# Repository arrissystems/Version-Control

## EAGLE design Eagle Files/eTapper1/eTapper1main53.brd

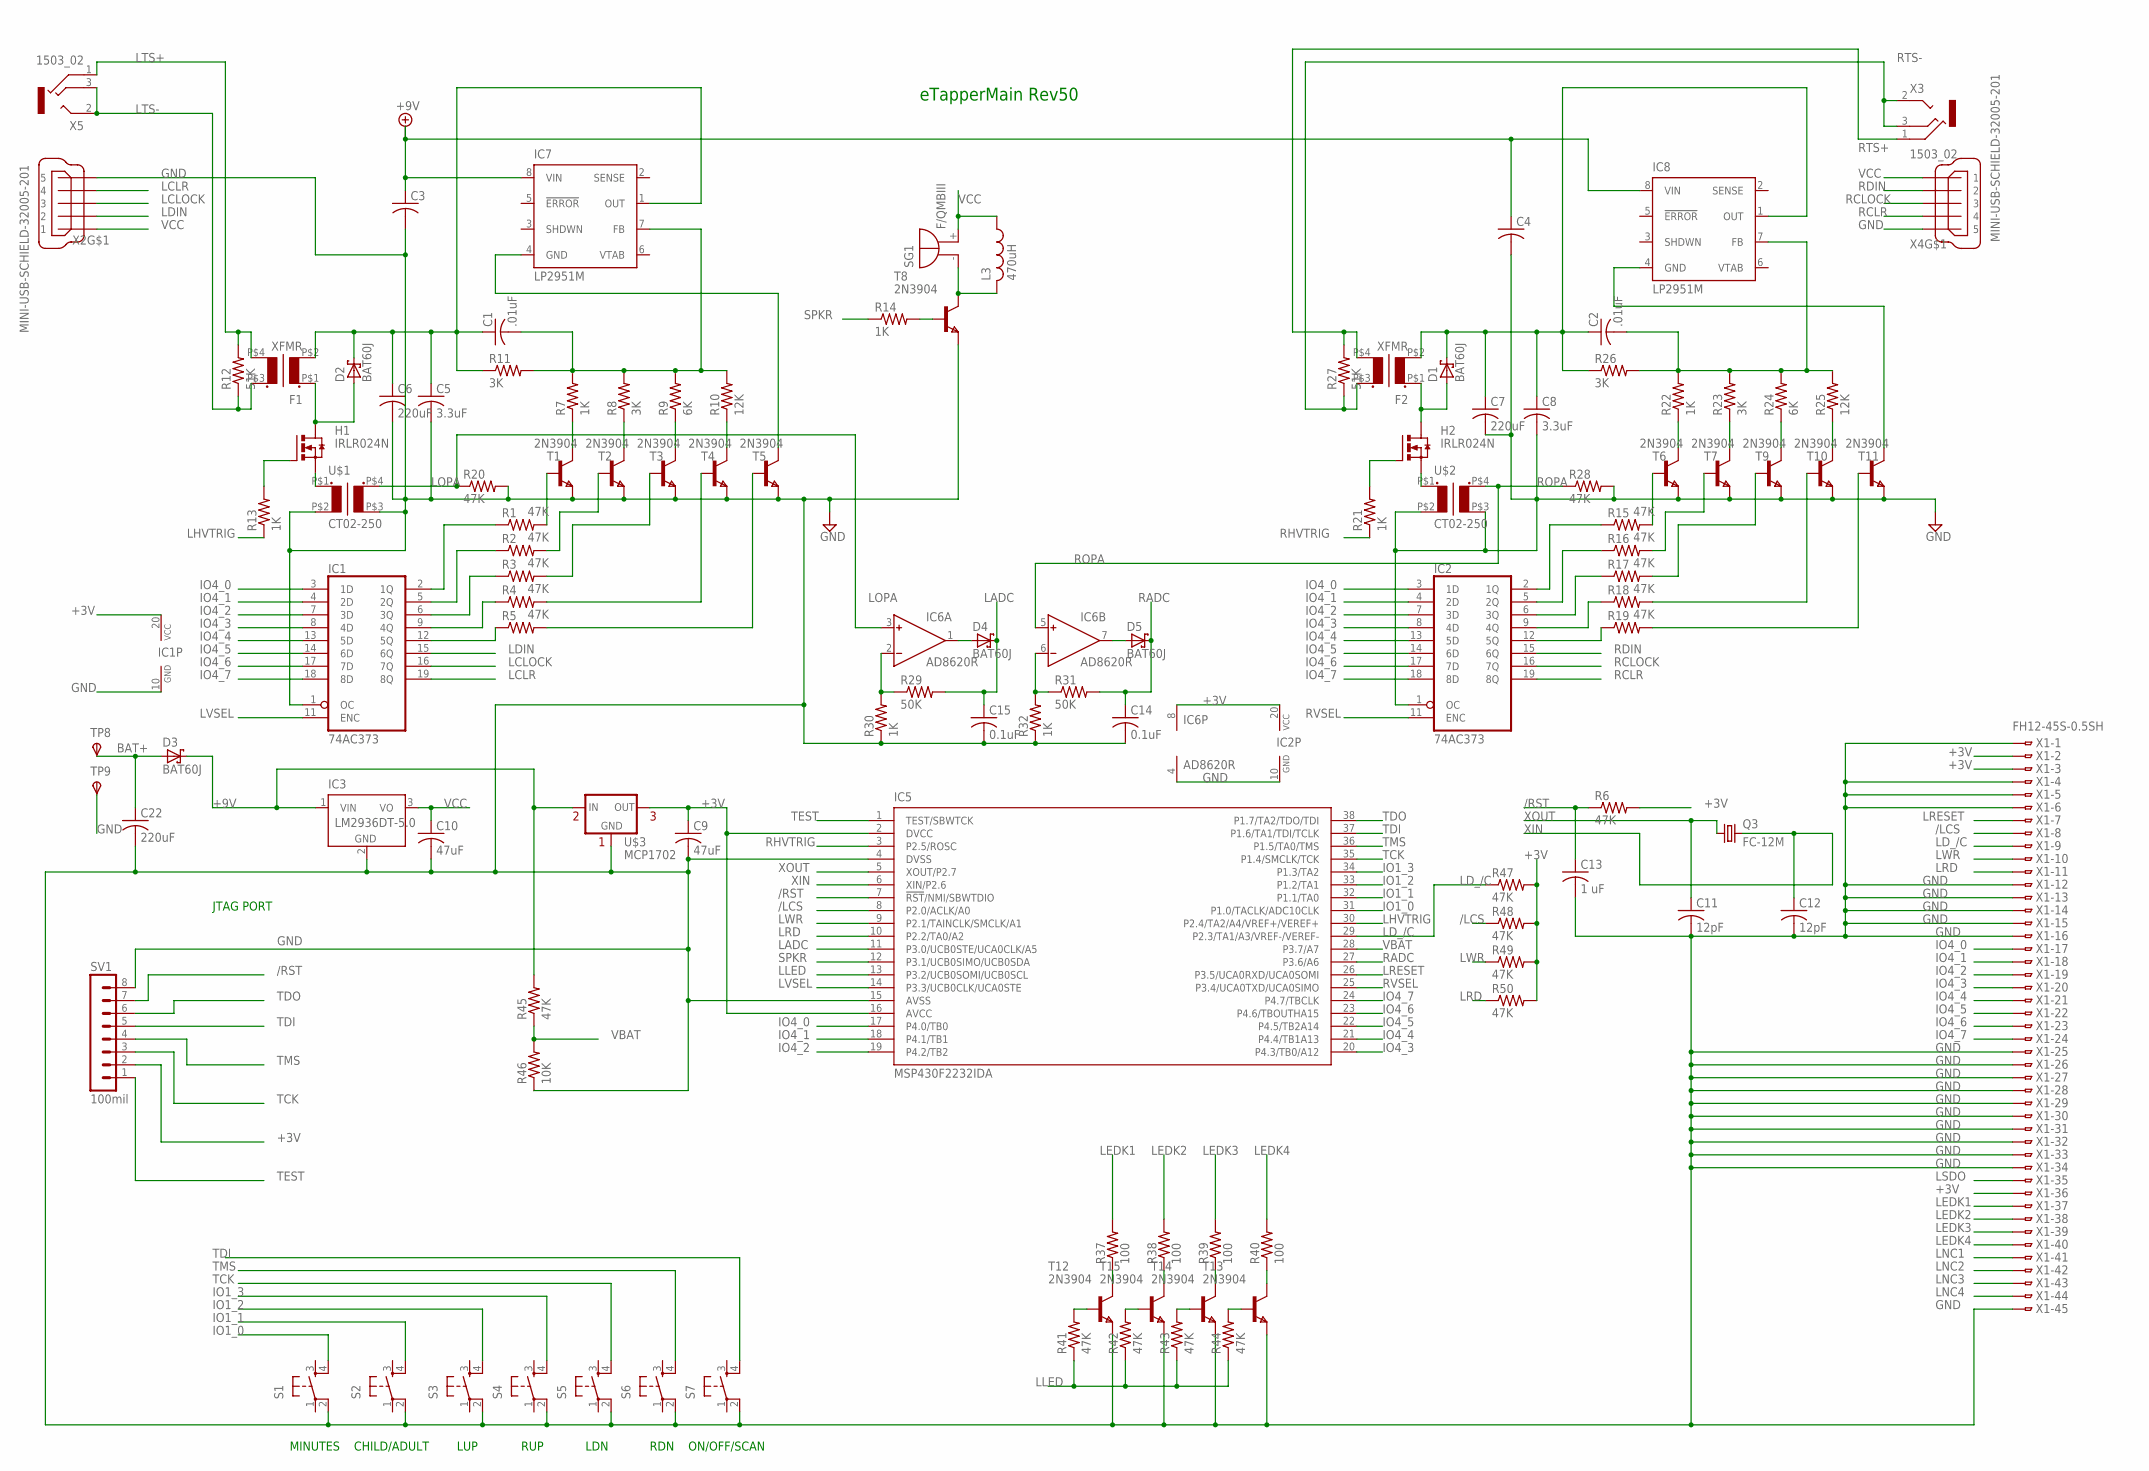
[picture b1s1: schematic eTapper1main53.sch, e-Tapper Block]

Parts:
C1, C2: .01uF; C0805
C3, C4: C-USC1206; C1206
C5, C8: 3.3uF; C0805
C6, C7, C22: 220uF; C1206
C9, C10: 47uF; C1206
C11, C12: 12pF; C0805
C13: 1 uF; C0805
C14, C15: 0.1uF; C0805
D1, D2, D3, D4, D5: BAT60J; SOD323_ST
F1, F2: XFMR
H1, H2: IRLR024N; D-PAK_TO252AA
IC1, IC2: 74AC373; SO20
IC3: LM2936DT-5.0; TO252
IC5: MSP430F2232IDA; TSSOP38_R-PDSO-G38-DA
IC6: AD8620R; SO8
IC7, IC8: LP2951M; SO08
L3: 470uH; L2825P
Q3: FC-12M
R1, R2, R3, R4, R5, R6, R15, R16, R17, R18, R19, R20, R28, R41, R42, R43, R44, R45, R47, R48, R49, R50: 47K; R0603
R7, R13, R14, R21, R22, R30, R32: 1K; R0603
R8, R11, R23, R26: 3K; R0603
R9, R24: 6K; R0603
R10, R25: 12K; R0603
R12, R27: 51K; R0603
R29, R31: 50K; R0603
R37, R38, R39, R40: 100; R0603
R46: 10K; R0603
S1, S2, S3, S4, S5, S6, S7: 10-XX; B3F-10XX
SG1: F/QMBIII
SV1: 100mil; MA08-1
T1, T2, T3, T4, T5, T6, T7, T8, T9, T10, T11, T12, T13, T14, T15: 2N3904; SOT-23
TP8, TP9: TPSPAD1-20; P1-20
U$1, U$2: CT02-250
U$3: MCP1702; TO92-
X1: FH12-45S-0.5SH
X2, X4: MINI-USB-SCHIELD-32005-201; 32005-201
X3, X5: 1503_02

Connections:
+3V: C9.1, IC1.20 (VCC), IC2.20 (VCC), IC5.2 (DVCC), IC5.16 (AVCC), IC6.8 (V+), R6.2, R47.2, R48.2, R49.2, R50.2, SV1.2, U$3.3 (OUT), X1.2, X1.3, X1.36
+9V: C3.1, C4.1, D3.C, IC3.1 (VIN), IC7.8 (VIN), IC8.8 (VIN), R45.2, U$3.2 (IN)
/LCS: IC5.8 (P2.0/ACLK/A0), R48.1, X1.8
/RST: C13.1, IC5.7 (!RST!/NMI/SBWTDIO), R6.1, SV1.7
BAT+: C22.1, D3.A, TP8.TP
GND: C3.2, C4.2, C5.2, C6.2, C7.2, C8.2, C9.2, C10.2, C11.2, C12.2, C13.2, C14.2, C15.2, C22.2, IC1.1 (OC), IC1.10 (GND), IC2.1 (OC), IC2.10 (GND), IC3.2 (GND), IC5.4 (DVSS), IC5.15 (AVSS), IC6.4 (V-), R20.2, R28.2, R30.1, R32.1, R46.1, S1.2 (P1), S2.2 (P1), S3.2 (P1), S4.2 (P1), S5.2 (P1), S6.2 (P1), S7.2 (P1), SV1.8, T1.2 (E), T2.2 (E), T3.2 (E), T4.2 (E), T5.2 (E), T6.2 (E), T7.2 (E), T8.2 (E), T9.2 (E), T10.2 (E), T11.2 (E), T12.2 (E), T13.2 (E), T14.2 (E), T15.2 (E), TP9.TP, U$1.P$2 (P2), U$1.P$3 (S2), U$2.P$2 (P2), U$2.P$3 (S2), U$3.1 (GND), X1.1, X1.4, X1.5, X1.6, X1.12, X1.13, X1.14, X1.15, X1.16, X1.25, X1.26, X1.27, X1.28, X1.29, X1.30, X1.31, X1.32, X1.33, X1.34, X1.45, X2.5, X4.5
IO1_0: IC5.31 (P1.0/TACLK/ADC10CLK), S1.4 (S1)
IO1_1: IC5.32 (P1.1/TA0), S2.4 (S1)
IO1_2: IC5.33 (P1.2/TA1), S3.4 (S1)
IO1_3: IC5.34 (P1.3/TA2), S4.4 (S1)
IO4_0: IC1.3 (1D), IC2.3 (1D), IC5.17 (P4.0/TB0), X1.17
IO4_1: IC1.4 (2D), IC2.4 (2D), IC5.18 (P4.1/TB1), X1.18
IO4_2: IC1.7 (3D), IC2.7 (3D), IC5.19 (P4.2/TB2), X1.19
IO4_3: IC1.8 (4D), IC2.8 (4D), IC5.20 (P4.3/TB0/A12), X1.20
IO4_4: IC1.13 (5D), IC2.13 (5D), IC5.21 (P4.4/TB1A13), X1.21
IO4_5: IC1.14 (6D), IC2.14 (6D), IC5.22 (P4.5/TB2A14), X1.22
IO4_6: IC1.17 (7D), IC2.17 (7D), IC5.23 (P4.6/TBOUTHA15), X1.23
IO4_7: IC1.18 (8D), IC2.18 (8D), IC5.24 (P4.7/TBCLK), X1.24
LADC: C15.1, D4.C, IC5.11 (P3.0/UCB0STE/UCA0CLK/A5), R29.2
LCLOCK: IC1.16 (7Q), X2.3
LCLR: IC1.19 (8Q), X2.4
LDIN: IC1.15 (6Q), X2.2
LD_/C: IC5.29 (P2.3/TA1/A3/VREF-/VEREF-), R47.1, X1.9
LEDK1: R37.2, X1.37
LEDK2: R38.2, X1.38
LEDK3: R39.2, X1.39
LEDK4: R40.2, X1.40
LHVTRIG: IC5.30 (P2.4/TA2/A4/VREF+/VEREF+), R13.1
LLED: IC5.13 (P3.2/UCB0SOMI/UCB0SCL), R41.1, R42.1, R43.1, R44.1
LNC1: X1.41
LNC2: X1.42
LNC3: X1.43
LNC4: X1.44
LOPA: IC6.3 (IN+), R20.1, U$1.P$4 (S1)
LRD: IC5.10 (P2.2/TA0/A2), R50.1, X1.11
LRESET: IC5.26 (P3.5/UCA0RXD/UCA0SOMI), X1.7
LSDO: X1.35
LTS+: F1.P$4 (S2), R12.2, X5.1
LTS-: F1.P$3 (S1), R12.1, X5.2, X5.3
LVSEL: IC1.11 (ENC), IC5.14 (P3.3/UCB0CLK/UCA0STE)
LWR: IC5.9 (P2.1/TAINCLK/SMCLK/A1), R49.1, X1.10
unnamed: IC1.2 (1Q), R1.1
unnamed: IC1.5 (2Q), R2.1
unnamed: IC1.6 (3Q), R3.1
unnamed: IC1.9 (4Q), R4.1
unnamed: IC1.12 (5Q), R5.1
unnamed: L3.2, SG1.- (+), T8.1 (C)
unnamed: R4.2, T4.3 (B)
unnamed: R5.2, T5.3 (B)
unnamed: D2.A, F1.P$1 (P1), H1.4 (D)
unnamed: R7.1, T1.1 (C)
unnamed: R8.1, T2.1 (C)
unnamed: R9.1, T3.1 (C)
unnamed: R1.2, T1.3 (B)
unnamed: R2.2, T2.3 (B)
unnamed: R3.2, T3.3 (B)
unnamed: R10.1, T4.1 (C)
unnamed: C1.2, IC7.7 (FB), R7.2, R8.2, R9.2, R10.2, R11.2
unnamed: C1.1, C5.1, C6.1, D2.C, F1.P$2 (P2), IC7.1 (OUT), R11.1
unnamed: D1.A, F2.P$1 (P1), H2.4 (D)
unnamed: IC2.2 (1Q), R15.1
unnamed: H1.1 (G), R13.2
unnamed: R14.2, T8.3 (B)
unnamed: H1.3 (S), U$1.P$1 (P1)
unnamed: IC2.5 (2Q), R16.1
unnamed: IC2.6 (3Q), R17.1
unnamed: IC2.9 (4Q), R18.1
unnamed: IC2.12 (5Q), R19.1
unnamed: R44.2, T13.3 (B)
unnamed: R15.2, T6.3 (B)
unnamed: R16.2, T7.3 (B)
unnamed: R17.2, T9.3 (B)
unnamed: R18.2, T10.3 (B)
unnamed: R19.2, T11.3 (B)
unnamed: D4.A, IC6.1 (OUT)
unnamed: R22.1, T6.1 (C)
unnamed: R23.1, T7.1 (C)
unnamed: R24.1, T9.1 (C)
unnamed: R25.1, T10.1 (C)
unnamed: C2.2, IC8.7 (FB), R22.2, R23.2, R24.2, R25.2, R26.2
unnamed: C2.1, C7.1, C8.1, D1.C, F2.P$2 (P2), IC8.1 (OUT), R26.1
unnamed: R37.1, T12.1 (C)
unnamed: H2.1 (G), R21.2
unnamed: R38.1, T15.1 (C)
unnamed: R39.1, T14.1 (C)
unnamed: IC7.4 (GND), T5.1 (C)
unnamed: R40.1, T13.1 (C)
unnamed: IC8.4 (GND), T11.1 (C)
unnamed: R43.2, T14.3 (B)
unnamed: R41.2, T12.3 (B)
unnamed: R42.2, T15.3 (B)
unnamed: H2.3 (S), U$2.P$1 (P1)
unnamed: IC6.6 (IN-), R31.1, R32.2
unnamed: IC6.2 (IN-), R29.1, R30.2
unnamed: D5.A, IC6.7 (OUT)
RADC: C14.1, D5.C, IC5.27 (P3.6/A6), R31.2
RCLOCK: IC2.16 (7Q), X4.3
RCLR: IC2.19 (8Q), X4.4
RDIN: IC2.15 (6Q), X4.2
RHVTRIG: IC5.3 (P2.5/ROSC), R21.1
ROPA: IC6.5 (IN+), R28.1, U$2.P$4 (S1)
RTS+: F2.P$4 (S2), R27.2, X3.1
RTS-: F2.P$3 (S1), R27.1, X3.2, X3.3
RVSEL: IC2.11 (ENC), IC5.25 (P3.4/UCA0TXD/UCA0SIMO)
SPKR: IC5.12 (P3.1/UCB0SIMO/UCB0SDA), R14.1
TCK: IC5.35 (P1.4/SMCLK/TCK), S5.4 (S1), SV1.3
TDI: IC5.37 (P1.6/TA1/TDI/TCLK), S7.4 (S1), SV1.5
TDO: IC5.38 (P1.7/TA2/TDO/TDI), SV1.6
TEST: IC5.1 (TEST/SBWTCK), SV1.1
TMS: IC5.36 (P1.5/TA0/TMS), S6.4 (S1), SV1.4
VBAT: IC5.28 (P3.7/A7), R45.1, R46.2
VCC: C10.1, IC3.3 (VO), L3.1, SG1.+ (-), X2.1, X4.1
XIN: C12.1, IC5.6 (XIN/P2.6), Q3.2
XOUT: C11.1, IC5.5 (XOUT/P2.7), Q3.1

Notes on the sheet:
ON/OFF/SCAN
MINUTES
CHILD/ADULT
LUP
RUP
JTAG PORT
LDN
RDN
eTapperMain Rev50

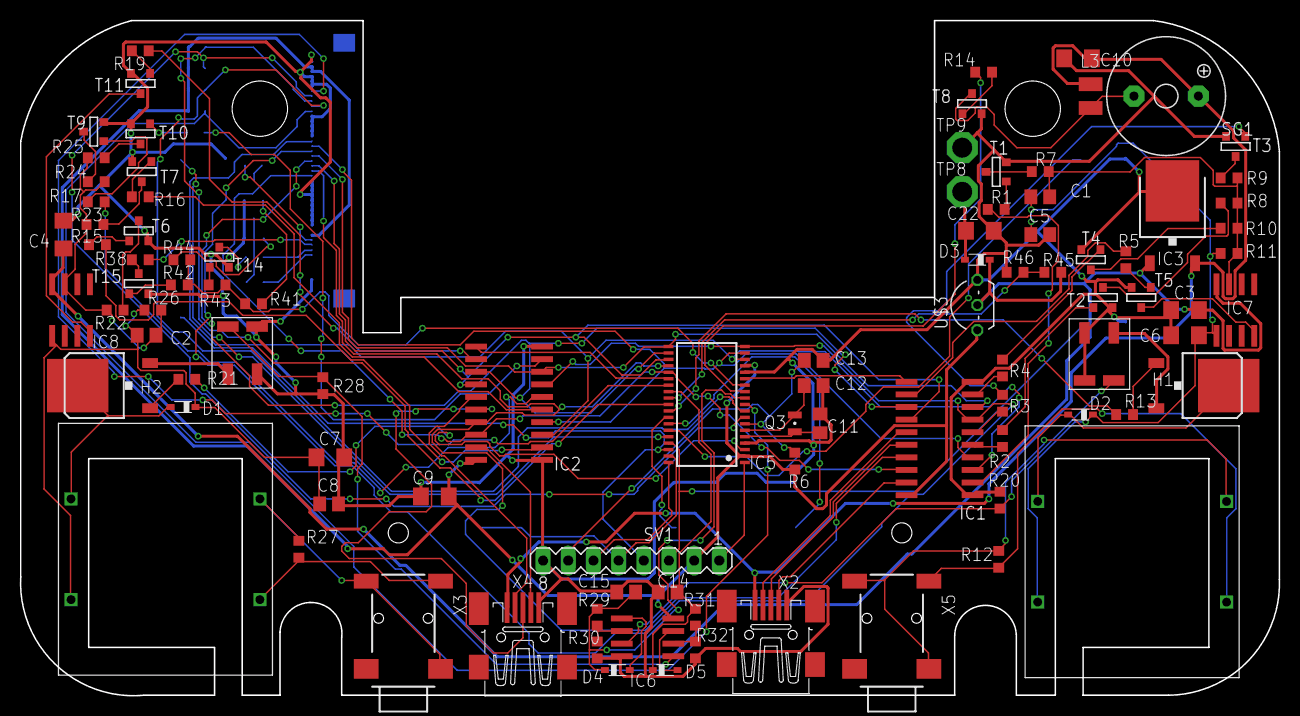
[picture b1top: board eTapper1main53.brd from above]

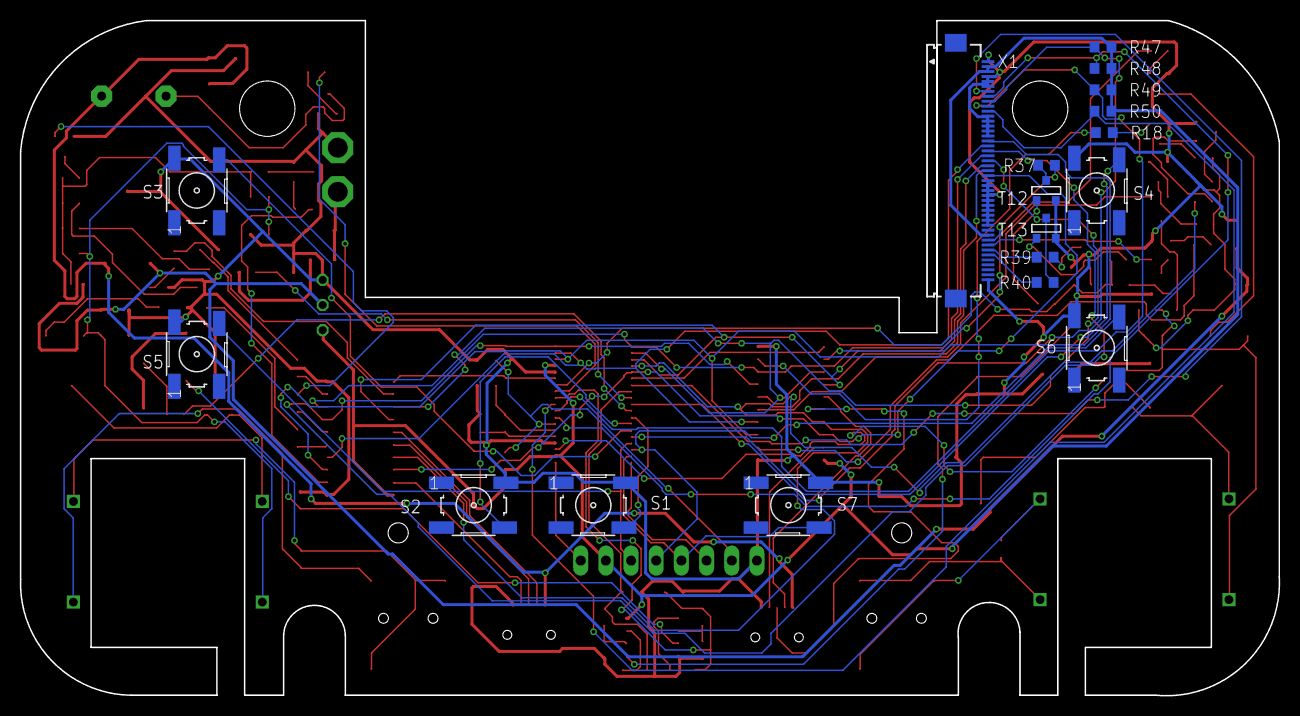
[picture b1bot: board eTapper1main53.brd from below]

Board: 2 copper layers, 127.0 x 68.1 mm, 115 parts (18 on the bottom side), 109 nets.

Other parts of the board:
DRILEGEND: DRILEGEND

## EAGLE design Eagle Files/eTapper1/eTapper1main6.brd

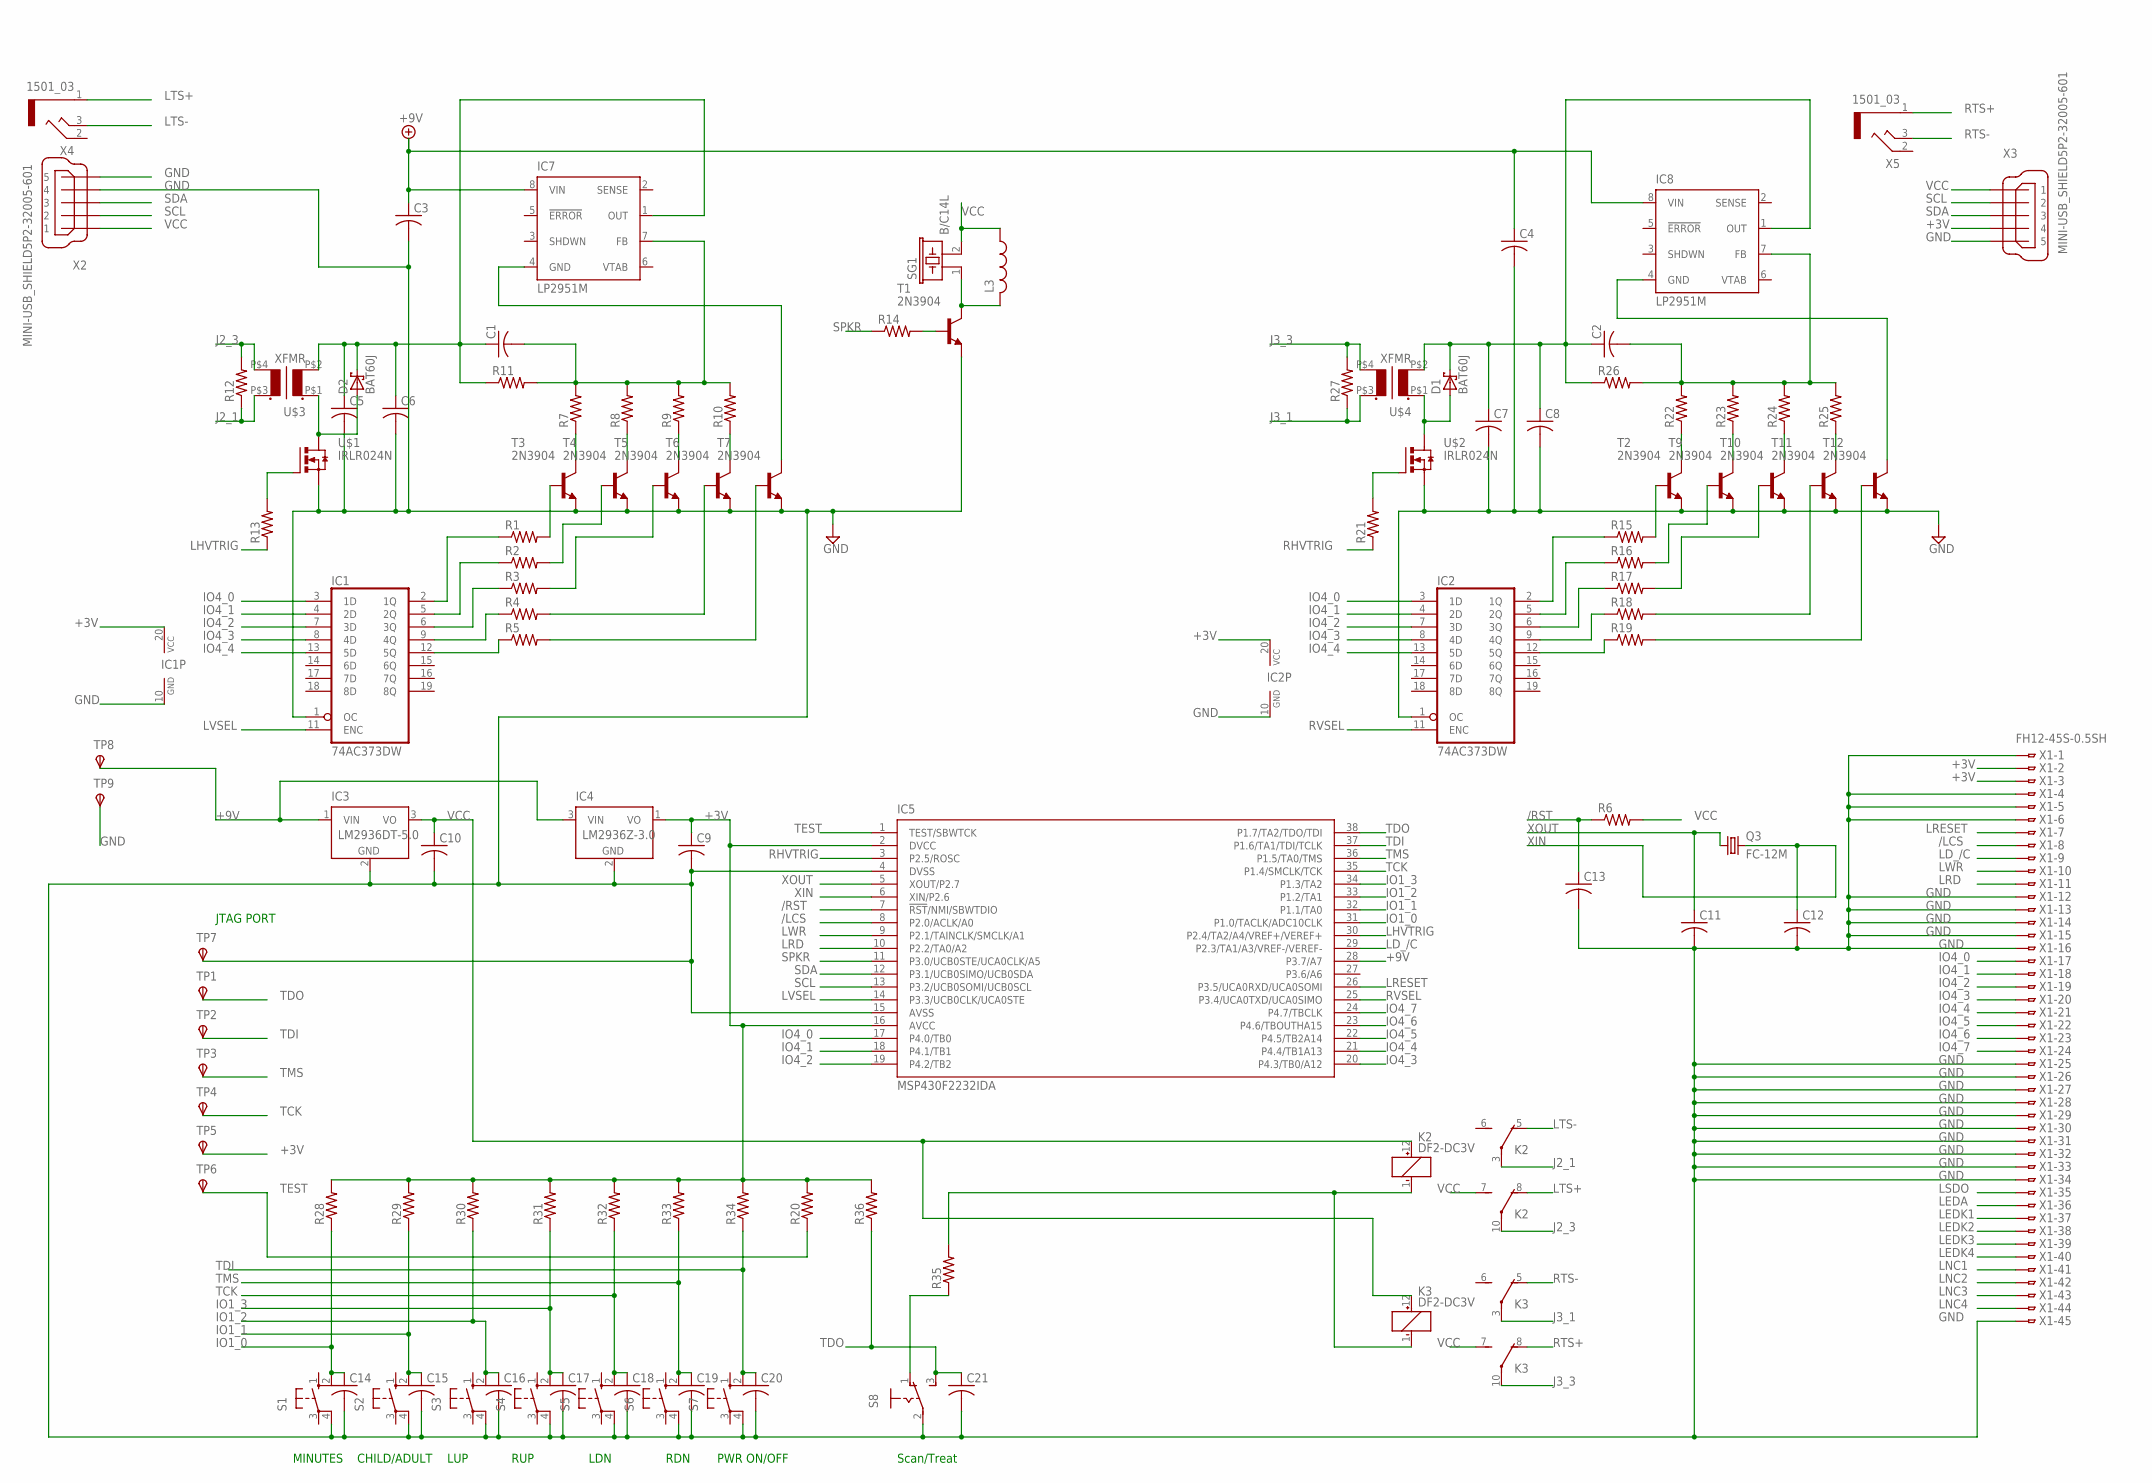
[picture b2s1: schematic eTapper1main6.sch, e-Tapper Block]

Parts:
C1, C2, C3, C4, C5, C6, C7, C8, C9, C10, C11, C12, C13, C14, C15, C16, C17, C18, C19, C20, C21: C-USC0805; C0805
D1, D2: BAT60J; SOD323_ST
IC1, IC2: 74AC373DW; SO20W
IC3: LM2936DT-5.0; TO252
IC4: LM2936Z-3.0; TO92
IC5: MSP430F2232IDA; TSSOP38_R-PDSO-G38-DA
IC7, IC8: LP2951M; SO08
K2, K3: DF2-DC3V; DF2
L3: L-USL2825P; L2825P
Q3: FC-12M
R1, R2, R3, R4, R5, R6, R7, R8, R9, R10, R11, R12, R13, R14, R15, R16, R17, R18, R19, R20, R21, R22, R23, R24, R25, R26, R27, R28, R29, R30, R31, R32, R33, R34, R35, R36: R-US_R0402; R0402
S1, S2, S3, S4, S5, S6, S7: 10-XX; B3F-10XX
S8: M251
SG1: B/C14L
T1, T2, T3, T4, T5, T6, T7, T9, T10, T11, T12: 2N3904; TO92
TP1, TP2, TP3, TP4, TP5, TP6, TP7, TP8, TP9: TPSTP06R; TP06R
U$1, U$2: IRLR024N; I-PAK_TO251AA
U$3, U$4: XFMR
X1: FH12-45S-0.5SH
X2, X3: MINI-USB_SHIELD5P2-32005-601; 32005-601
X4, X5: 1501_03

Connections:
+3V: C9.1, IC1.20 (VCC), IC2.20 (VCC), IC4.1 (VO), IC5.2 (DVCC), IC5.16 (AVCC), R20.2, R28.2, R29.2, R30.2, R31.2, R32.2, R33.2, R34.2, R36.2, TP5.TP, X1.2, X1.3, X3.4
+9V: C3.1, C4.1, IC3.1 (VIN), IC4.3 (VIN), IC5.28 (P3.7/A7), IC7.8 (VIN), IC8.8 (VIN), TP8.TP
/LCS: IC5.8 (P2.0/ACLK/A0), X1.8
/RST: C13.1, IC5.7 (!RST!/NMI/SBWTDIO), R6.1
GND: C3.2, C4.2, C5.2, C6.2, C7.2, C8.2, C9.2, C10.2, C11.2, C12.2, C13.2, C14.2, C15.2, C16.2, C17.2, C18.2, C19.2, C20.2, C21.2, IC1.1 (OC), IC1.10 (GND), IC2.1 (OC), IC2.10 (GND), IC3.2 (GND), IC4.2 (GND), IC5.4 (DVSS), IC5.15 (AVSS), S1.4 (P1), S2.4 (P1), S3.4 (P1), S4.4 (P1), S5.4 (P1), S6.4 (P1), S7.4 (P1), S8.2, T1.3 (E), T2.3 (E), T3.3 (E), T4.3 (E), T5.3 (E), T6.3 (E), T7.3 (E), T9.3 (E), T10.3 (E), T11.3 (E), T12.3 (E), TP7.TP, TP9.TP, U$1.3 (S), U$2.3 (S), X1.1, X1.4, X1.5, X1.6, X1.12, X1.13, X1.14, X1.15, X1.16, X1.25, X1.26, X1.27, X1.28, X1.29, X1.30, X1.31, X1.32, X1.33, X1.34, X1.45, X2.4, X2.5, X3.5
IO1_0: C14.1, IC5.31 (P1.0/TACLK/ADC10CLK), R28.1, S1.2 (S1)
IO1_1: C15.1, IC5.32 (P1.1/TA0), R29.1, S2.2 (S1)
IO1_2: C16.1, IC5.33 (P1.2/TA1), R30.1, S3.2 (S1)
IO1_3: C17.1, IC5.34 (P1.3/TA2), R31.1, S4.2 (S1)
IO4_0: IC1.3 (1D), IC2.3 (1D), IC5.17 (P4.0/TB0), X1.17
IO4_1: IC1.4 (2D), IC2.4 (2D), IC5.18 (P4.1/TB1), X1.18
IO4_2: IC1.7 (3D), IC2.7 (3D), IC5.19 (P4.2/TB2), X1.19
IO4_3: IC1.8 (4D), IC2.8 (4D), IC5.20 (P4.3/TB0/A12), X1.20
IO4_4: IC1.13 (5D), IC2.13 (5D), IC5.21 (P4.4/TB1A13), X1.21
IO4_5: IC5.22 (P4.5/TB2A14), X1.22
IO4_6: IC5.23 (P4.6/TBOUTHA15), X1.23
IO4_7: IC5.24 (P4.7/TBCLK), X1.24
J2_1: K2.3, R12.1, U$3.P$3 (S1)
J2_3: K2.10, R12.2, U$3.P$4 (S2)
J3_1: K3.3, R27.1, U$4.P$3 (S1)
J3_3: K3.10, R27.2, U$4.P$4 (S2)
LD_/C: IC5.29 (P2.3/TA1/A3/VREF-/VEREF-), X1.9
LEDA: X1.36
LEDK1: X1.37
LEDK2: X1.38
LEDK3: X1.39
LEDK4: X1.40
LHVTRIG: IC5.30 (P2.4/TA2/A4/VREF+/VEREF+), R13.1
LNC1: X1.41
LNC2: X1.42
LNC3: X1.43
LNC4: X1.44
LRD: IC5.10 (P2.2/TA0/A2), X1.11
LRESET: IC5.26 (P3.5/UCA0RXD/UCA0SOMI), X1.7
LSDO: X1.35
LTS+: K2.8 (O), X4.1
LTS-: K2.5 (O), X4.3
LVSEL: IC1.11 (ENC), IC5.14 (P3.3/UCB0CLK/UCA0STE)
LWR: IC5.9 (P2.1/TAINCLK/SMCLK/A1), X1.10
unnamed: IC1.2 (1Q), R1.1
unnamed: IC1.5 (2Q), R2.1
unnamed: IC1.6 (3Q), R3.1
unnamed: IC1.9 (4Q), R4.1
unnamed: IC1.12 (5Q), R5.1
unnamed: L3.2, SG1.1, T1.1 (C)
unnamed: R4.2, T6.2 (B)
unnamed: R5.2, T7.2 (B)
unnamed: D2.A, U$1.2 (D), U$1.4 (D), U$3.P$1 (P1)
unnamed: R7.1, T3.1 (C)
unnamed: R8.1, T4.1 (C)
unnamed: R9.1, T5.1 (C)
unnamed: R1.2, T3.2 (B)
unnamed: R2.2, T4.2 (B)
unnamed: R3.2, T5.2 (B)
unnamed: R10.1, T6.1 (C)
unnamed: C1.2, IC7.7 (FB), R7.2, R8.2, R9.2, R10.2, R11.2
unnamed: C1.1, C5.1, C6.1, D2.C, IC7.1 (OUT), R11.1, U$3.P$2 (P2)
unnamed: D1.A, U$2.2 (D), U$2.4 (D), U$4.P$1 (P1)
unnamed: IC2.2 (1Q), R15.1
unnamed: R13.2, U$1.1 (G)
unnamed: R14.2, T1.2 (B)
unnamed: R35.1, S8.1 (O)
unnamed: IC2.5 (2Q), R16.1
unnamed: IC2.6 (3Q), R17.1
unnamed: IC2.9 (4Q), R18.1
unnamed: IC2.12 (5Q), R19.1
unnamed: R15.2, T2.2 (B)
unnamed: R16.2, T9.2 (B)
unnamed: R17.2, T10.2 (B)
unnamed: R18.2, T11.2 (B)
unnamed: R19.2, T12.2 (B)
unnamed: K2.1 (-), K3.1 (-), R35.2
unnamed: R22.1, T2.1 (C)
unnamed: R23.1, T9.1 (C)
unnamed: R24.1, T10.1 (C)
unnamed: R25.1, T11.1 (C)
unnamed: C2.2, IC8.7 (FB), R22.2, R23.2, R24.2, R25.2, R26.2
unnamed: C2.1, C7.1, C8.1, D1.C, IC8.1 (OUT), R26.1, U$4.P$2 (P2)
unnamed: R21.2, U$2.1 (G)
unnamed: IC7.4 (GND), T7.1 (C)
unnamed: IC8.4 (GND), T12.1 (C)
RHVTRIG: IC5.3 (P2.5/ROSC), R21.1
RTS+: K3.8 (O), X5.1
RTS-: K3.5 (O), X5.3
RVSEL: IC2.11 (ENC), IC5.25 (P3.4/UCA0TXD/UCA0SIMO)
SCL: IC5.13 (P3.2/UCB0SOMI/UCB0SCL), X2.2, X3.2
SDA: IC5.12 (P3.1/UCB0SIMO/UCB0SDA), X2.3, X3.3
SPKR: IC5.11 (P3.0/UCB0STE/UCA0CLK/A5), R14.1
TCK: C18.1, IC5.35 (P1.4/SMCLK/TCK), R32.1, S5.2 (S1), TP4.TP
TDI: C20.1, IC5.37 (P1.6/TA1/TDI/TCLK), R34.1, S7.2 (S1), TP2.TP
TDO: C21.1, IC5.38 (P1.7/TA2/TDO/TDI), R36.1, S8.3 (S), TP1.TP
TEST: IC5.1 (TEST/SBWTCK), R20.1, TP6.TP
TMS: C19.1, IC5.36 (P1.5/TA0/TMS), R33.1, S6.2 (S1), TP3.TP
VCC: C10.1, IC3.3 (VO), K2.7 (S), K2.12 (+), K3.7 (S), K3.12 (+), L3.1, R6.2, SG1.2, X2.1, X3.1
XIN: C12.1, IC5.6 (XIN/P2.6), Q3.2
XOUT: C11.1, IC5.5 (XOUT/P2.7), Q3.1

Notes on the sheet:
PWR ON/OFF
Scan/Treat
MINUTES
CHILD/ADULT
LUP
RUP
JTAG PORT
LDN
RDN

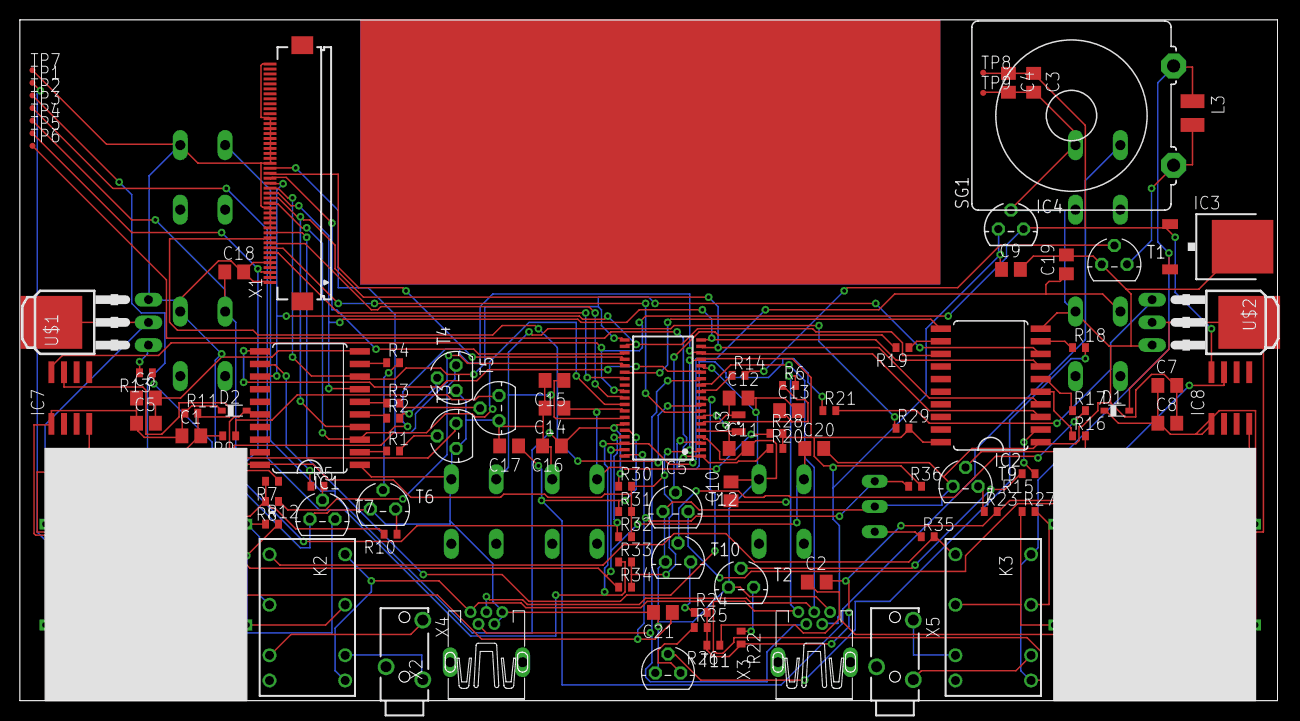
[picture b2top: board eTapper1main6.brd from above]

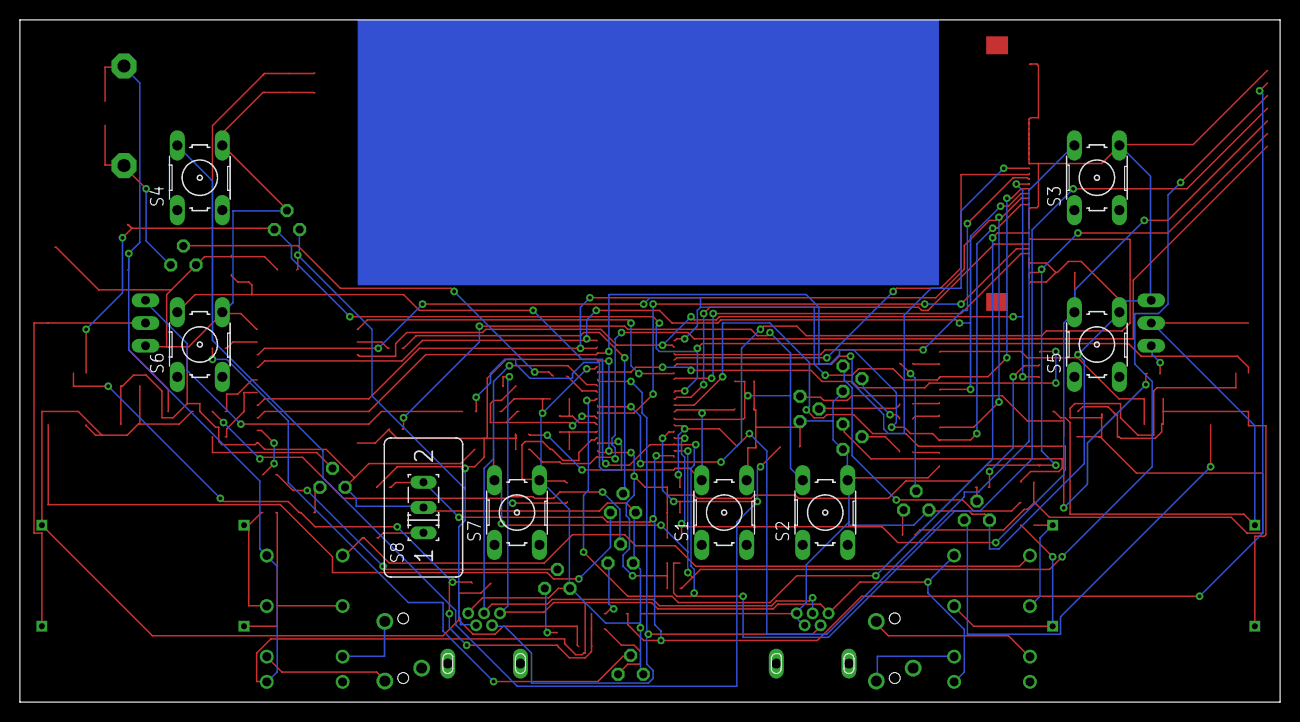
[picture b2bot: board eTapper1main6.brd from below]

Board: 2 copper layers, 126.7 x 68.6 mm, 108 parts (8 on the bottom side), 86 nets.

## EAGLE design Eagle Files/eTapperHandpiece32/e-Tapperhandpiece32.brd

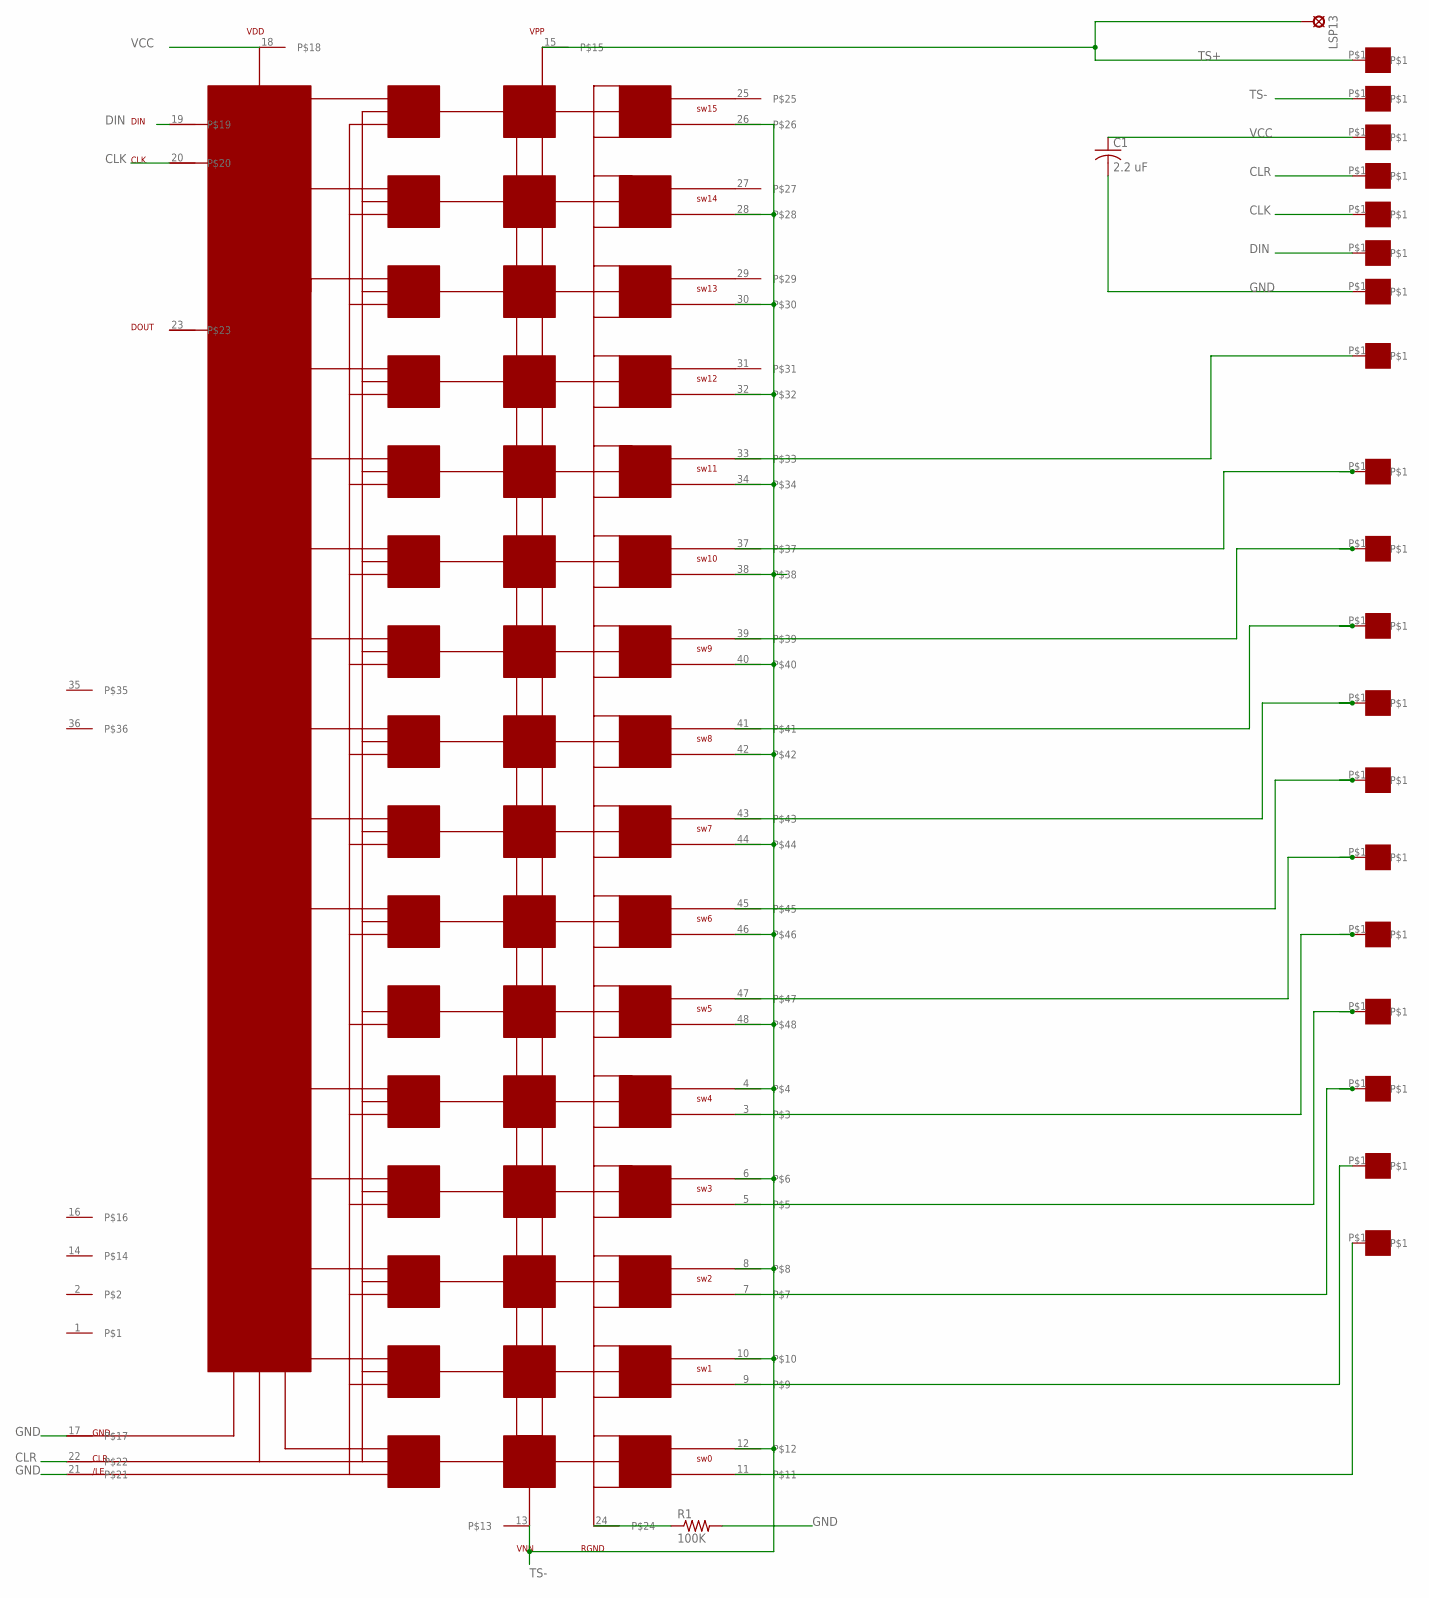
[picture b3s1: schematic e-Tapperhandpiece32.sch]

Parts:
C1: 2.2 uF; C0805
LSP13: SE11
R1: 100K; R0603
TSP1, TSP2, TSP3, TSP4, TSP5, TSP6, TSP7, TSP8, TSP9, TSP10, TSP11, TSP12, TSP13, TSP14, TSP16, TSP17, TSP18, TSP19: ET1
U1: CPC7701; LQFP48
VCC: ET1

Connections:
CLK: TSP17.P$1, U1.20
CLR: TSP18.P$1, U1.22
DIN: TSP16.P$1, U1.19
GND: C1.2, R1.2, TSP19.P$1, U1.17, U1.21
unnamed: R1.1, U1.24
unnamed: TSP1.P$1, U1.33
unnamed: TSP2.P$1, U1.37
unnamed: TSP3.P$1, U1.39
unnamed: TSP4.P$1, U1.41
unnamed: TSP5.P$1, U1.43
unnamed: TSP6.P$1, U1.45
unnamed: TSP7.P$1, U1.47
unnamed: TSP8.P$1, U1.3
unnamed: TSP9.P$1, U1.5
unnamed: TSP10.P$1, U1.7
unnamed: TSP11.P$1, U1.9
unnamed: TSP12.P$1, U1.11
TS+: LSP13.MP, TSP13.P$1, U1.15
TS-: TSP14.P$1, U1.4, U1.6, U1.8, U1.10, U1.12, U1.13, U1.26, U1.28, U1.30, U1.32, U1.34, U1.38, U1.40, U1.42, U1.44, U1.46, U1.48
VCC: C1.1, U1.18, VCC.P$1

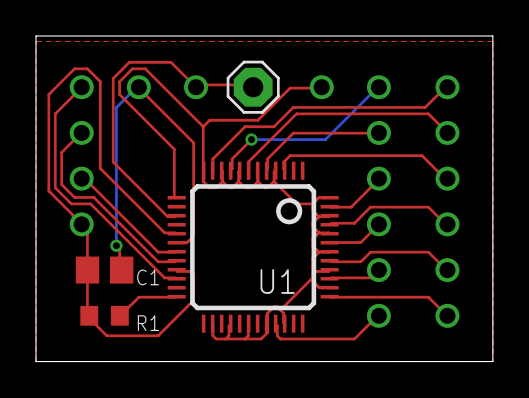
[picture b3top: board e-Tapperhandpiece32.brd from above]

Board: 2 copper layers, 25.4 x 18.1 mm, 23 parts (0 on the bottom side), 20 nets.

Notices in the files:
Eagle Files/eTapperHandpiece32/e-Tapperhandpiece32.brd:
e-Tapper Handpiece R32 @All rights reserved
